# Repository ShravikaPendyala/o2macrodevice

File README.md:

# o2macrodevice
Anderson Lab @ MIT

Author: Shravika Pendyala
When: UROP for Summer of 2024

17 July 2024
Code form July 4 = Perfect + Working

19 June 2024

Right now, the only code used to upload to the ST Nucleo is main.c located in 
(NUCLEO-L476RG/Applications/NFC08A1_PollingTagDetectNDEF/Src/main.c)

The NFC06A1 is not used anywhere

Task: 
Determine what aspects of the Nucleo-L476RG are actually necessary to just power the NFC08A1 board + start thinking about designing a board that does the minimum required to power the NFC board. 

INSTRUCTIONS TO DOWNLOAD/SETUP
1. https://www.st.com/en/embedded-software/x-cube-nfc6.html : Download driver (has example code in it)
2. Extract the STM32 Folder inside the project you wan't to install. (Not the whole NDEFPolling folder, this will create build errors)

BOARDS INFO
1. In my personal file system, the folders are an accurate representation of the primary chip used in the project

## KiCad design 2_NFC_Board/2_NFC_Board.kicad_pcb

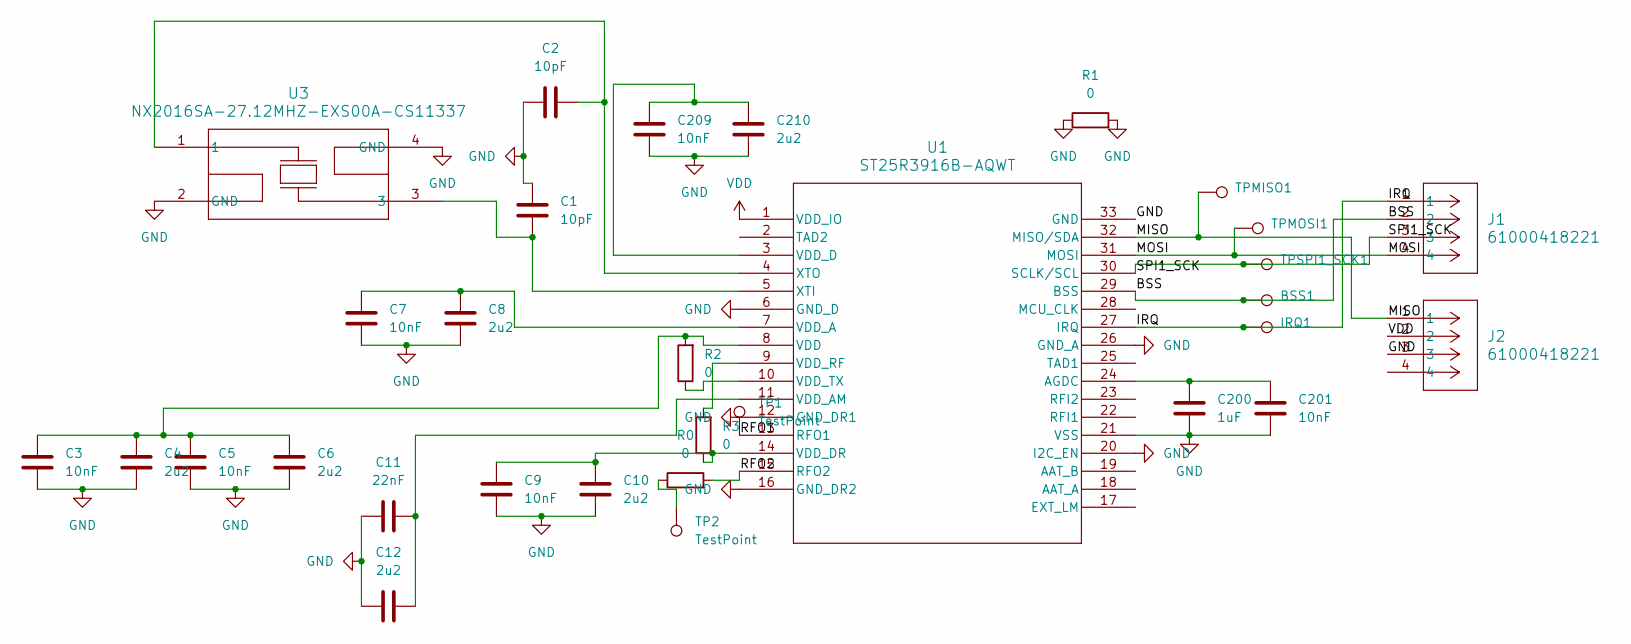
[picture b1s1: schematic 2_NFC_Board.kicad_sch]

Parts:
BSS1: TestPoint_Pad_2.0x2.0mm
C1, C2: 10pF; C_0402_1005Metric_Pad0.74x0.62mm_HandSolder
C3, C5, C7, C9, C201, C209: 10nF; C_0402_1005Metric_Pad0.74x0.62mm_HandSolder
C4, C6, C8, C10, C12, C210: 2u2; C_0402_1005Metric_Pad0.74x0.62mm_HandSolder
C11: 22nF; C_0402_1005Metric_Pad0.74x0.62mm_HandSolder
C200: 1uF; C_0402_1005Metric_Pad0.74x0.62mm_HandSolder
IRQ1: TestPoint_Pad_2.0x2.0mm
J1, J2: 61000418221; 61000418221_WRE
R0, R1, R2, R3: 0; R_0402_1005Metric_Pad0.72x0.64mm_HandSolder
TP1, TP2: TestPoint; TestPoint_Pad_2.0x2.0mm
TPMISO1: TestPoint_Pad_2.0x2.0mm
TPMOSI1: TestPoint_Pad_2.0x2.0mm
TPSPI1_SCK1: TestPoint_Pad_2.0x2.0mm
U1: ST25R3916B-AQWT; VFQFPN32_5X5_WETTABLE_STM
U3: NX2016SA-27.12MHZ-EXS00A-CS11337; SMD04_NX2016S_NDK

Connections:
/BSS: BSS1.1, J1.2, U1.29 (BSS)
/IRQ: IRQ1.1, J1.1, U1.27 (IRQ)
/MISO: J2.1, TPMISO1.1, U1.32 (MISO/SDA)
/MOSI: J1.4, TPMOSI1.1, U1.31 (MOSI)
/RFO1: TP1.1, U1.13 (RFO1)
/RFO2: R0.2, U1.15 (RFO2)
/SPI1_SCK: J1.3, TPSPI1_SCK1.1, U1.30 (SCLK/SCL)
GND: C1.1, C2.2, C3.2, C4.2, C5.2, C6.2, C7.2, C8.2, C9.2, C10.2, C11.2, C12.2, C200.1, C201.2, C209.2, C210.2, J2.3, R1.1, R1.2, U1.6 (GND_D), U1.12 (GND_DR1), U1.16 (GND_DR2), U1.20 (I2C_EN), U1.21 (VSS), U1.26 (GND_A), U1.33 (GND), U3.2 (GND), U3.4 (GND)
unnamed: R0.1, TP2.1
unnamed: C200.2, C201.1, U1.24 (AGDC)
unnamed: C3.1, C4.1, C5.1, C6.1, R2.2, U1.8 (VDD)
unnamed: C7.1, C8.1, U1.7 (VDD_A)
unnamed: C11.1, C12.1, U1.11 (VDD_AM)
unnamed: C209.1, C210.1, U1.3 (VDD_D)
unnamed: C9.1, C10.1, R3.1, U1.14 (VDD_DR)
unnamed: R3.2, U1.9 (VDD_RF)
unnamed: R2.1, U1.10 (VDD_TX)
unnamed: C1.2, U1.5 (XTI), U3.3
unnamed: C2.1, U1.4 (XTO), U3.1
VDD: J2.2, U1.1 (VDD_IO)

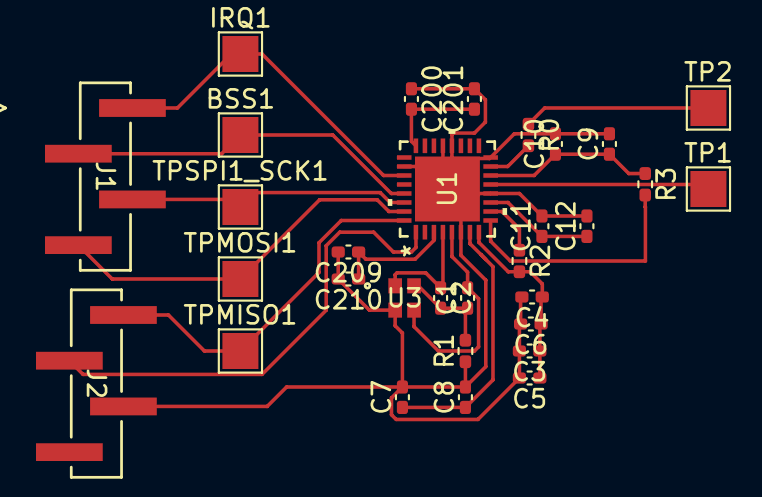
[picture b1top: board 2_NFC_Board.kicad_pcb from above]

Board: 2 copper layers, 31 parts (0 on the bottom side), 20 nets.

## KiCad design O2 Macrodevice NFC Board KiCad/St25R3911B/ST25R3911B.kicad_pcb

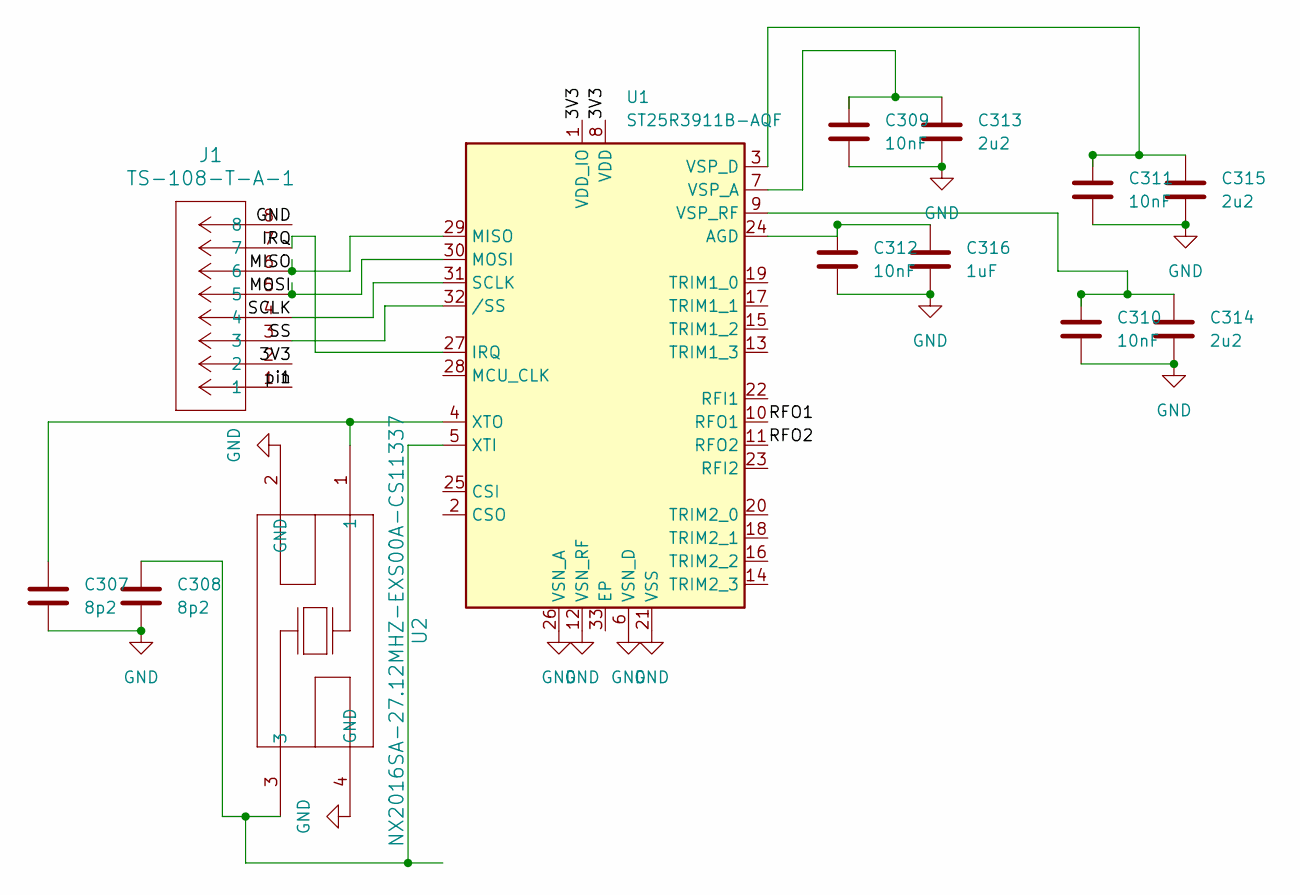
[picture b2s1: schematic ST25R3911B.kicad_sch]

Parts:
C307, C308: 8p2; C_0402_1005Metric_Pad0.74x0.62mm_HandSolder
C309, C310, C311, C312: 10nF; C_0402_1005Metric_Pad0.74x0.62mm_HandSolder
C313, C314, C315: 2u2; C_0402_1005Metric_Pad0.74x0.62mm_HandSolder
C316: 1uF; C_0402_1005Metric_Pad0.74x0.62mm_HandSolder
J1: TS-108-T-A-1; CON8_1X8_TUC_HTS_SAI
U1: ST25R3911B-AQF; QFN-32-1EP_5x5mm_P0.5mm_EP3.6x3.6mm_ThermalVias
U2: NX2016SA-27.12MHZ-EXS00A-CS11337; SMD04_NX2016S_NDK

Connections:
/1: J1.1
/3V3: J1.2, U1.1 (VDD_IO), U1.8 (VDD)
/IRQ: J1.7, U1.27 (IRQ)
/MISO: J1.6, U1.29 (MISO)
/MOSI: J1.5, U1.30 (MOSI)
/RFO1: U1.10 (RFO1)
/RFO2: U1.11 (RFO2)
/SCLK: J1.4, U1.31 (SCLK)
/SS: J1.3, U1.32 (/SS)
GND: C307.2, C308.2, C309.2, C310.2, C311.2, C312.2, C313.2, C314.2, C315.2, C316.2, J1.8, U1.6 (VSN_D), U1.12 (VSN_RF), U1.21 (VSS), U1.26 (VSN_A), U2.2 (GND), U2.4 (GND)
unnamed: C312.1, C316.1, U1.24 (AGD)
unnamed: C309.1, C313.1, U1.7 (VSP_A)
unnamed: C311.1, C315.1, U1.3 (VSP_D)
unnamed: C310.1, C314.1, U1.9 (VSP_RF)
unnamed: C308.1, U1.5 (XTI), U2.3
unnamed: C307.1, U1.4 (XTO), U2.1

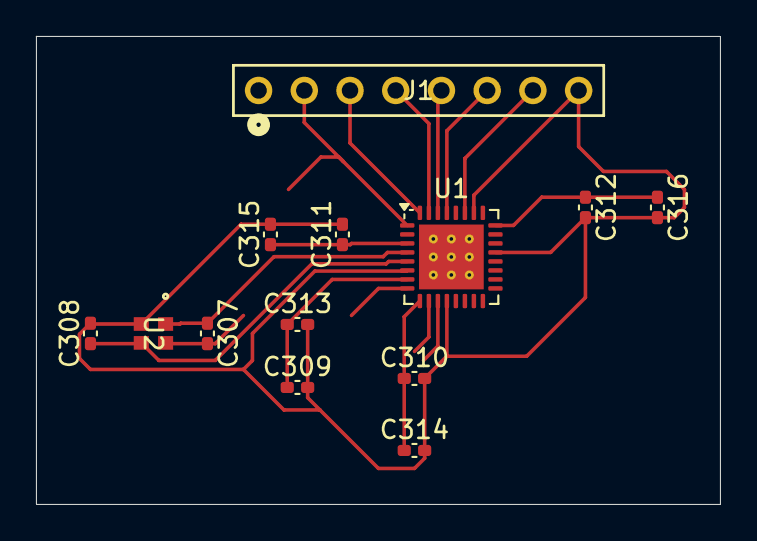
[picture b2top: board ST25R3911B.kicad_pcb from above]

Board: 2 copper layers, 38.0 x 26.0 mm, 13 parts (0 on the bottom side), 13 nets.

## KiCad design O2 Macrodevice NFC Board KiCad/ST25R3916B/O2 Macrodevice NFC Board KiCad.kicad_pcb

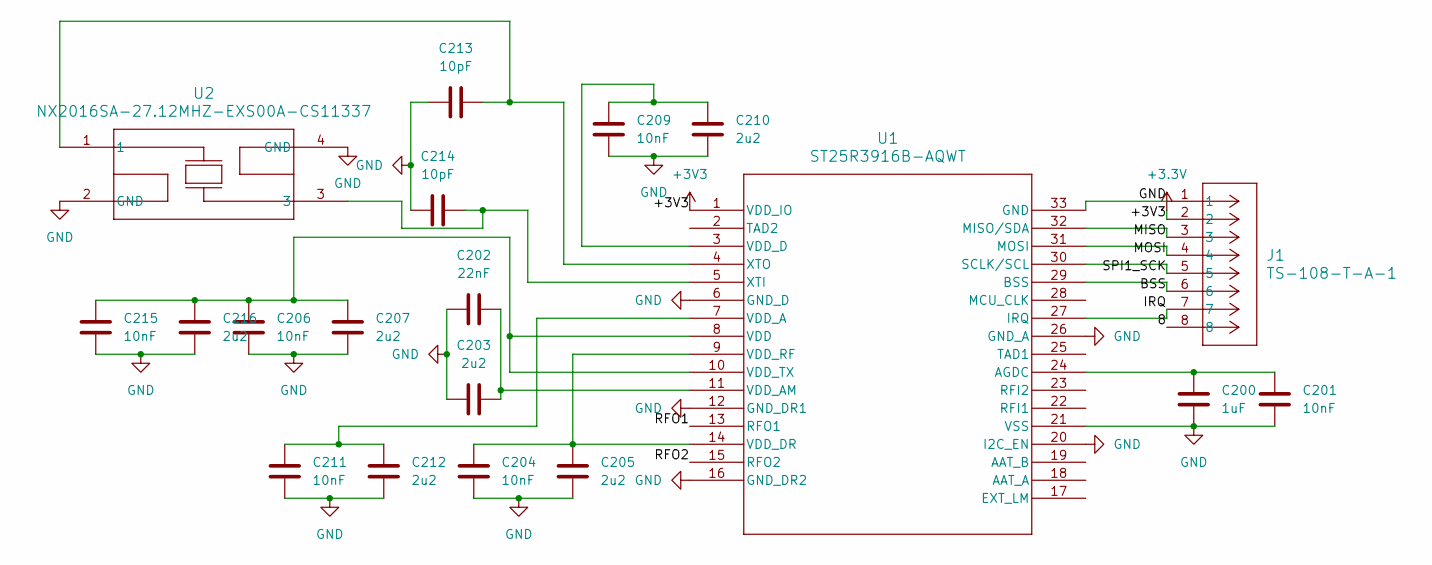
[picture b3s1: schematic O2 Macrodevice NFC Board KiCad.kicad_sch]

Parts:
C200: 1uF; C_0402_1005Metric_Pad0.74x0.62mm_HandSolder
C201, C204, C206, C209, C211, C215: 10nF; C_0402_1005Metric_Pad0.74x0.62mm_HandSolder
C202: 22nF; C_0402_1005Metric_Pad0.74x0.62mm_HandSolder
C203, C205, C207, C210, C212, C216: 2u2; C_0402_1005Metric_Pad0.74x0.62mm_HandSolder
C213, C214: 10pF; C_0402_1005Metric_Pad0.74x0.62mm_HandSolder
J1: TS-108-T-A-1; CON8_1X8_TUC_HTS_SAI
U1: ST25R3916B-AQWT; VFQFPN32_5X5_WETTABLE_STM
U2: NX2016SA-27.12MHZ-EXS00A-CS11337; SMD04_NX2016S_NDK

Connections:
+3.3V: J1.2, U1.1 (VDD_IO)
/8: J1.8
/BSS: J1.6, U1.29 (BSS)
/IRQ: J1.7, U1.27 (IRQ)
/MISO: J1.3, U1.32 (MISO/SDA)
/MOSI: J1.4, U1.31 (MOSI)
/RFO1: U1.13 (RFO1)
/RFO2: U1.15 (RFO2)
/SPI1_SCK: J1.5, U1.30 (SCLK/SCL)
GND: C200.1, C201.2, C202.2, C203.2, C204.2, C205.2, C206.2, C207.2, C209.2, C210.2, C211.2, C212.2, C213.2, C214.2, C215.2, C216.2, J1.1, U1.6 (GND_D), U1.12 (GND_DR1), U1.16 (GND_DR2), U1.20 (I2C_EN), U1.21 (VSS), U1.26 (GND_A), U1.33 (GND), U2.2 (GND), U2.4 (GND)
unnamed: C200.2, C201.1, U1.24 (AGDC)
unnamed: C206.1, C207.1, C215.1, C216.1, U1.8 (VDD), U1.10 (VDD_TX)
unnamed: C211.1, C212.1, U1.7 (VDD_A)
unnamed: C202.1, C203.1, U1.11 (VDD_AM)
unnamed: C209.1, C210.1, U1.3 (VDD_D)
unnamed: C204.1, C205.1, U1.9 (VDD_RF), U1.14 (VDD_DR)
unnamed: C214.1, U1.5 (XTI), U2.3
unnamed: C213.1, U1.4 (XTO), U2.1

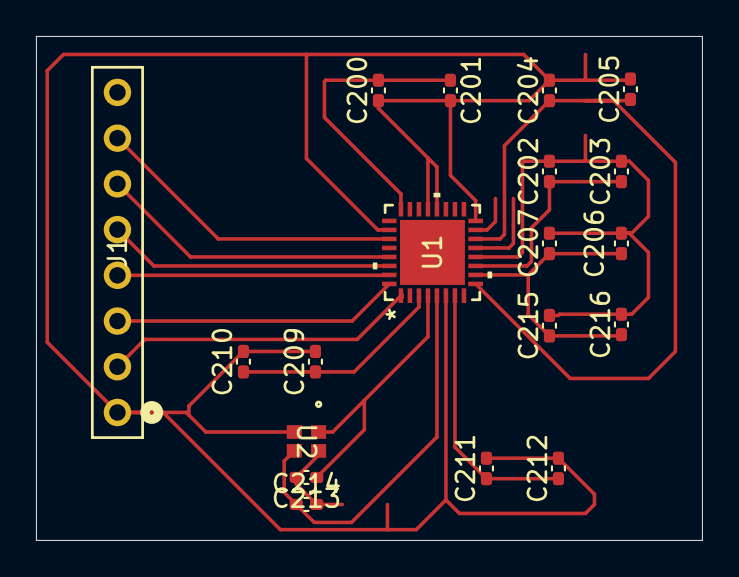
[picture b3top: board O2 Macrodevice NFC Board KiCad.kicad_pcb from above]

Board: 2 copper layers, 37.0 x 28.0 mm, 19 parts (0 on the bottom side), 15 nets.

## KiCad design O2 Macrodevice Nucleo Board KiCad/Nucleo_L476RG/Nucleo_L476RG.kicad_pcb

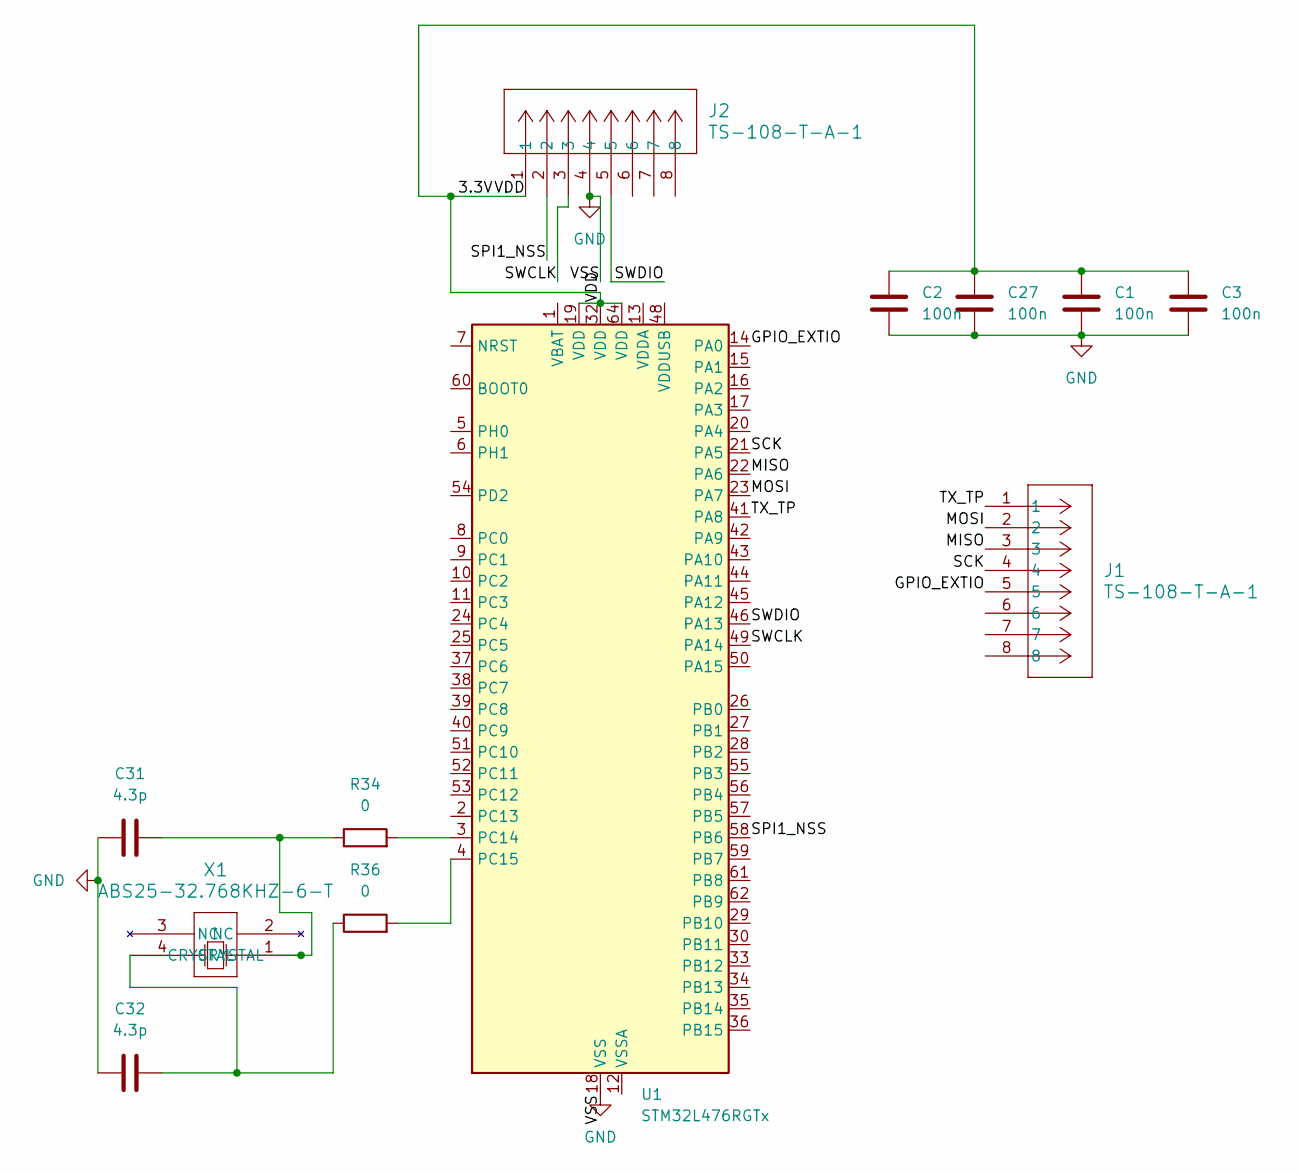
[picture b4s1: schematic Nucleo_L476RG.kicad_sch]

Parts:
C1, C2, C3, C27: 100n; C_0402_1005Metric_Pad0.74x0.62mm_HandSolder
C31, C32: 4.3p; C_0402_1005Metric_Pad0.74x0.62mm_HandSolder
J1, J2: TS-108-T-A-1; CON8_1X8_TUC_HTS_SAI
R34, R36: 0; R_0402_1005Metric_Pad0.72x0.64mm_HandSolder
U1: STM32L476RGTx; LQFP-64_10x10mm_P0.5mm
X1: ABS25-32.768KHZ-6-T; X_ABS25_ABR

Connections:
/<NO NET>: C1.2, C2.2, C3.2, C27.2, J2.1, U1.19 (VDD), U1.32 (VDD), U1.64 (VDD)
/GPIO_EXTIO: J1.5, U1.14 (PA0)
/MISO: J1.3, U1.22 (PA6)
/MOSI: J1.2, U1.23 (PA7)
/SCK: J1.4, U1.21 (PA5)
/SPI1_NSS: J2.2, U1.58 (PB6)
/SWCLK: J2.3, U1.49 (PA14)
/SWDIO: J2.5, U1.46 (PA13)
/TX_TP: J1.1, U1.41 (PA8)
GND: C1.1, C2.1, C3.1, C27.1, C31.1, C32.1, J2.4, U1.18 (VSS), U1.31 (VSS), U1.47 (VSS), U1.63 (VSS)
unnamed: C31.2, R34.1, X1.1 (CRYSTAL)
unnamed: C32.2, R36.1, X1.4 (CRYSTAL)
unnamed: R34.2, U1.3 (PC14)
unnamed: R36.2, U1.4 (PC15)

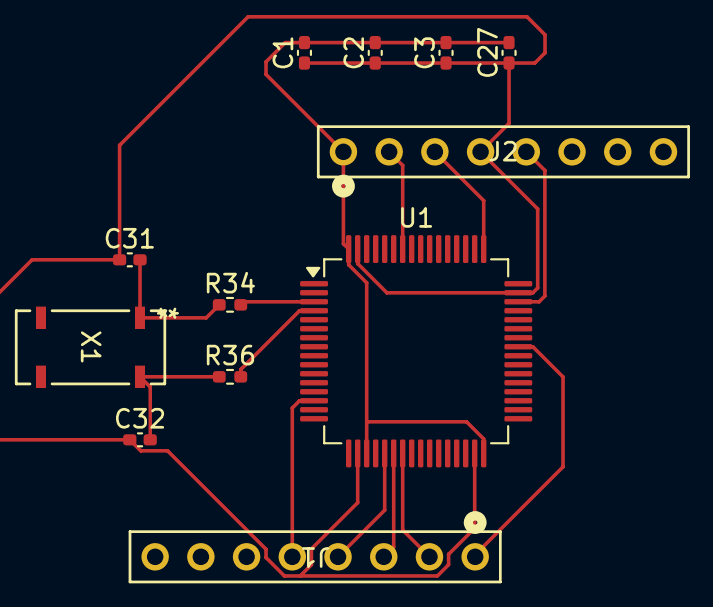
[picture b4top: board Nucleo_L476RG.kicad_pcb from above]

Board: 2 copper layers, 12 parts (0 on the bottom side), 14 nets.

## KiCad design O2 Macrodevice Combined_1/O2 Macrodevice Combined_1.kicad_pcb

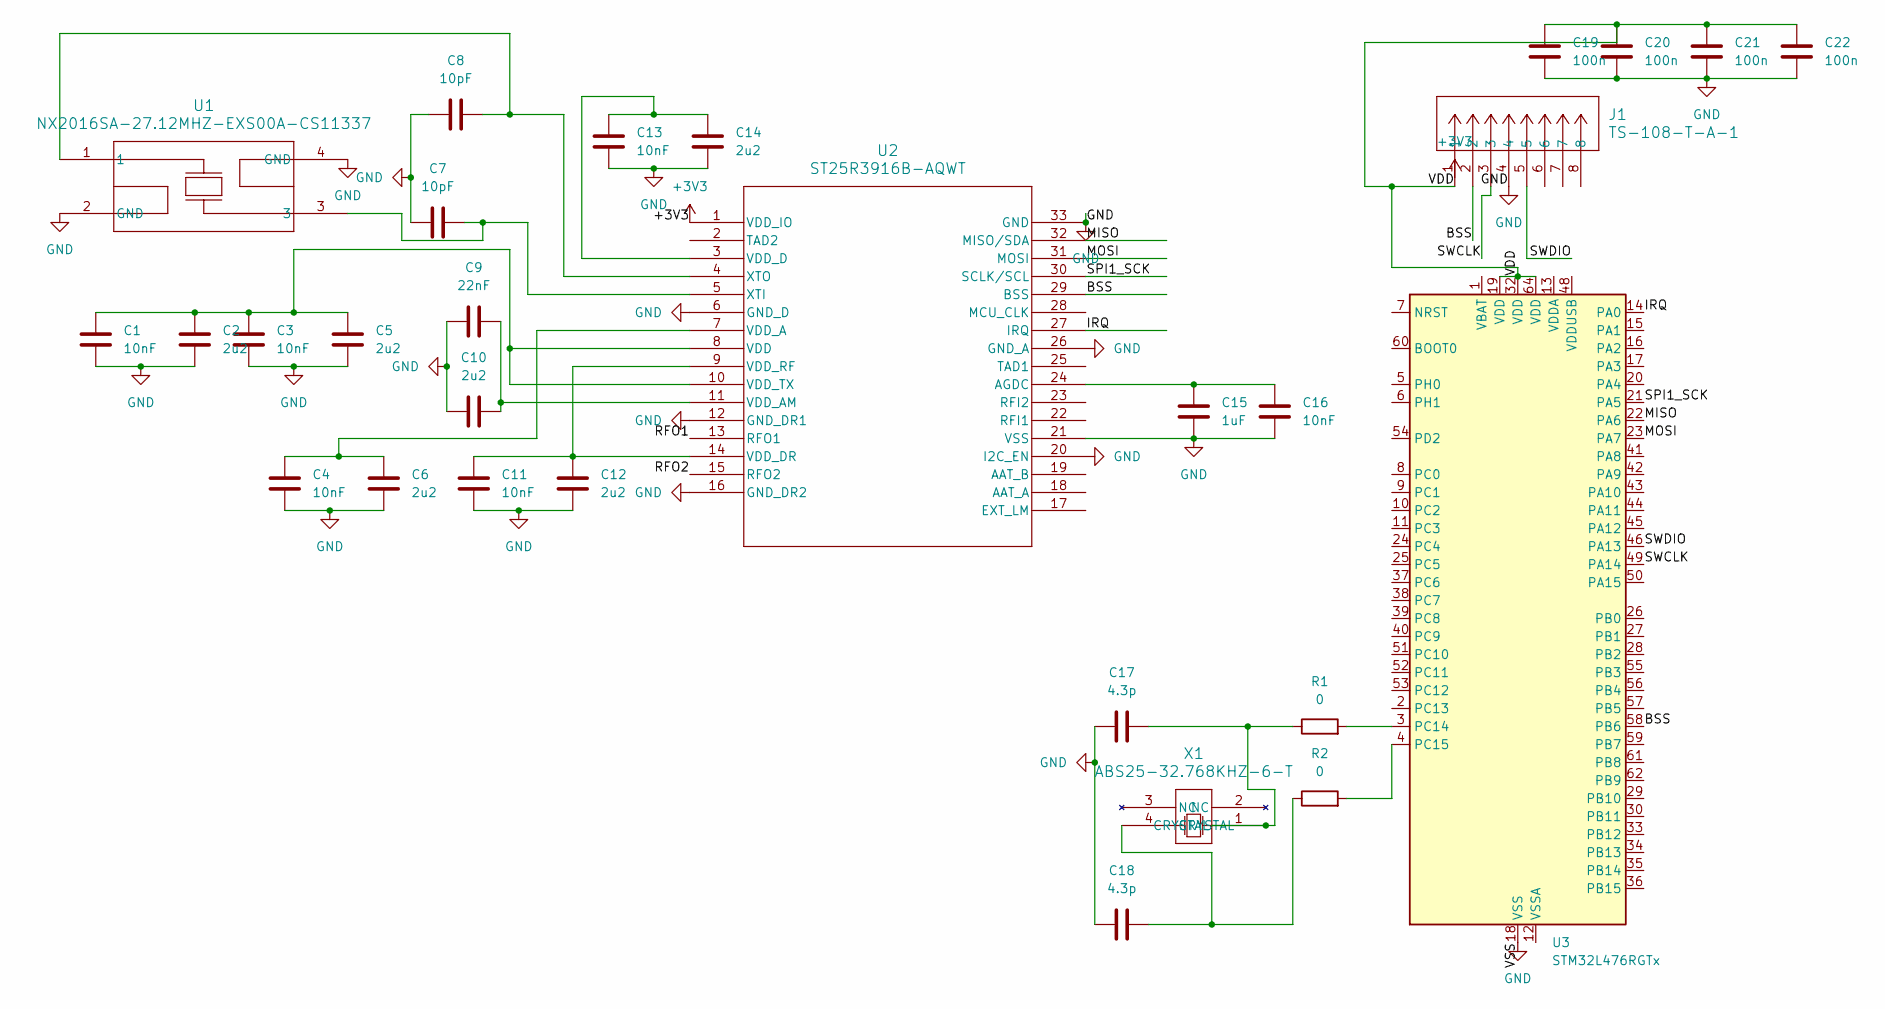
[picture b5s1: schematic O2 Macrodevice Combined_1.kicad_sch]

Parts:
C1, C3, C4, C11, C13, C16: 10nF; C_0402_1005Metric_Pad0.74x0.62mm_HandSolder
C2, C5, C6, C10, C12, C14: 2u2; C_0402_1005Metric_Pad0.74x0.62mm_HandSolder
C7, C8: 10pF; C_0402_1005Metric_Pad0.74x0.62mm_HandSolder
C9: 22nF; C_0402_1005Metric_Pad0.74x0.62mm_HandSolder
C15: 1uF; C_0402_1005Metric_Pad0.74x0.62mm_HandSolder
C17, C18: 4.3p; C_0402_1005Metric_Pad0.74x0.62mm_HandSolder
C19, C20, C21, C22: 100n; C_0402_1005Metric_Pad0.74x0.62mm_HandSolder
J1: TS-108-T-A-1; CON8_1X8_TUC_HTS_SAI
R1, R2: 0; R_0402_1005Metric_Pad0.72x0.64mm_HandSolder
U1: NX2016SA-27.12MHZ-EXS00A-CS11337; SMD04_NX2016S_NDK
U2: ST25R3916B-AQWT; VFQFPN32_5X5_WETTABLE_STM
U3: STM32L476RGTx; LQFP-64_10x10mm_P0.5mm
X1: ABS25-32.768KHZ-6-T; X_ABS25_ABR

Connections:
+3V3: U2.1 (VDD_IO)
/<NO NET>: C19.2, C20.2, C21.2, C22.2, J1.1, U3.19 (VDD), U3.32 (VDD), U3.64 (VDD)
/BSS: J1.2, U2.29 (BSS), U3.58 (PB6)
/IRQ: U2.27 (IRQ), U3.14 (PA0)
/MISO: U2.32 (MISO/SDA), U3.22 (PA6)
/MOSI: U2.31 (MOSI), U3.23 (PA7)
/RFO1: U2.13 (RFO1)
/RFO2: U2.15 (RFO2)
/SPI1_SCK: U2.30 (SCLK/SCL), U3.21 (PA5)
/SWCLK: J1.3, U3.49 (PA14)
/SWDIO: J1.5, U3.46 (PA13)
GND: C1.2, C2.2, C3.2, C4.2, C5.2, C6.2, C7.2, C8.2, C9.2, C10.2, C11.2, C12.2, C13.2, C14.2, C15.1, C16.2, C17.1, C18.1, C19.1, C20.1, C21.1, C22.1, J1.4, U1.2 (GND), U1.4 (GND), U2.6 (GND_D), U2.12 (GND_DR1), U2.16 (GND_DR2), U2.20 (I2C_EN), U2.21 (VSS), U2.26 (GND_A), U2.33 (GND), U3.18 (VSS), U3.31 (VSS), U3.47 (VSS), U3.63 (VSS)
unnamed: C17.2, R1.1, X1.1 (CRYSTAL)
unnamed: C18.2, R2.1, X1.4 (CRYSTAL)
unnamed: C15.2, C16.1, U2.24 (AGDC)
unnamed: C1.1, C2.1, C3.1, C5.1, U2.8 (VDD), U2.10 (VDD_TX)
unnamed: C4.1, C6.1, U2.7 (VDD_A)
unnamed: C9.1, C10.1, U2.11 (VDD_AM)
unnamed: C13.1, C14.1, U2.3 (VDD_D)
unnamed: C11.1, C12.1, U2.9 (VDD_RF), U2.14 (VDD_DR)
unnamed: C7.1, U1.3, U2.5 (XTI)
unnamed: C8.1, U1.1, U2.4 (XTO)
unnamed: R1.2, U3.3 (PC14)
unnamed: R2.2, U3.4 (PC15)

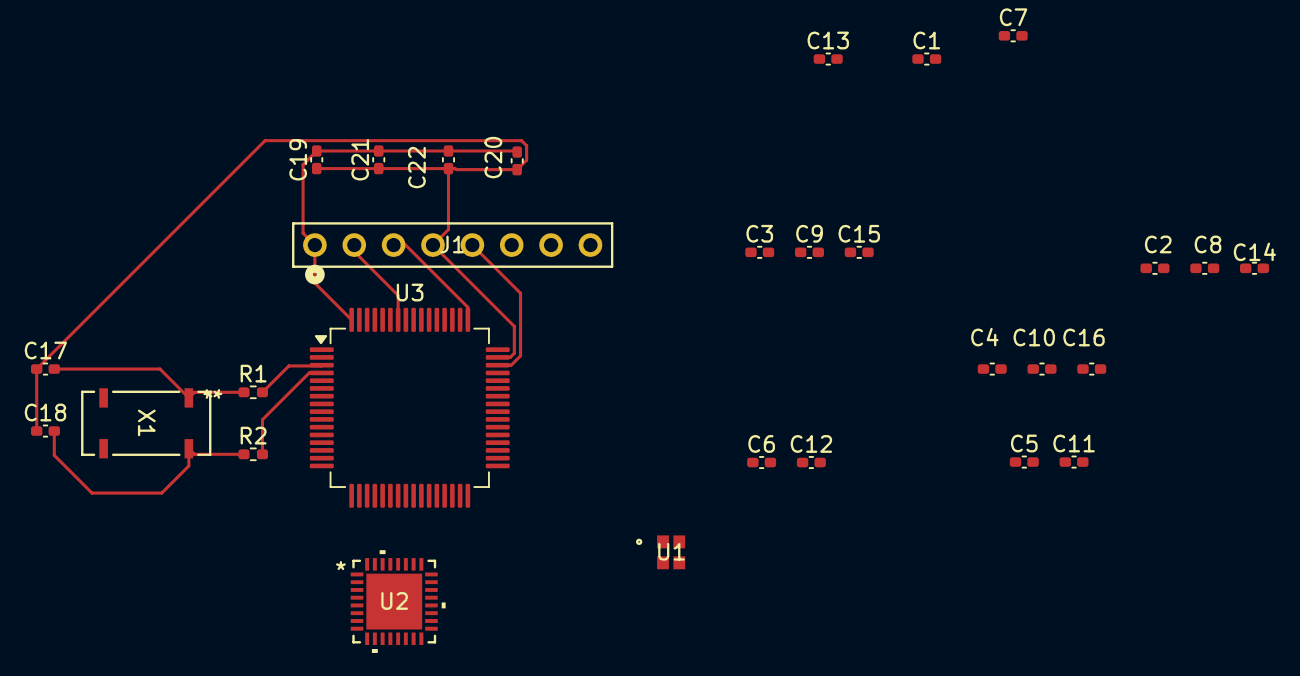
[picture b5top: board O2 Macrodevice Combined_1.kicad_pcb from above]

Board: 2 copper layers, 29 parts (0 on the bottom side), 21 nets.

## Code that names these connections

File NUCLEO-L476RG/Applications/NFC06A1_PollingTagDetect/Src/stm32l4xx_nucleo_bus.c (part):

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
    __HAL_RCC_GPIOA_CLK_ENABLE();
    /**SPI1 GPIO Configuration
    PA5     ------> SPI1_SCK
    PA6     ------> SPI1_MISO
    PA7     ------> SPI1_MOSI
    */
    GPIO_InitStruct.Pin = BUS_SPI1_SCK_GPIO_PIN;
    GPIO_InitStruct.Mode = GPIO_MODE_AF_PP;
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    __HAL_RCC_SPI1_CLK_DISABLE();

    /**SPI1 GPIO Configuration
    PA5     ------> SPI1_SCK
    PA6     ------> SPI1_MISO
    PA7     ------> SPI1_MOSI
    */
    HAL_GPIO_DeInit(BUS_SPI1_SCK_GPIO_PORT, BUS_SPI1_SCK_GPIO_PIN);

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
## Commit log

2024-06-19 initial file transfer onto github from the lab laptop ST32CubeIDE
2024-06-19 uploaded specsheets
2024-06-19 Create ProgressLog.txt
    maintain day-to-day work progress
2024-06-19 Update ProgressLog.txt 6_19_24
2024-06-23 upload
2024-06-23 OG files from example
2024-06-23 log update
2024-06-23 made some changes (deleted config pins experimentally)
2024-07-02 Add files via upload
    Files from Src folder
2024-07-26 Basic Info about boards
2024-07-28 uploading all PCB boards
2024-07-31 july 31 update
2024-07-31 power consumption as of July 31
2024-08-17 Aug 17 update
2024-08-19 pics of current consumption from LabView software using 2 separate MY boards
2024-08-19 labeled charts of current consumption (NOT Combined - 2 separate Nucleo + NFC boards)
2024-08-23 August 23 Update
2024-08-23 Update 23 August
2024-08-23 Update August 23 with power consumption

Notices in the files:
NUCLEO-L476RG/Applications/NFC06A1_PollingTagDetect/Src/stm32l4xx_nucleo_bus.c:
Copyright (c) 2023 STMicroelectronics.
All rights reserved.
This software is licensed under terms that can be found in the LICENSE file
